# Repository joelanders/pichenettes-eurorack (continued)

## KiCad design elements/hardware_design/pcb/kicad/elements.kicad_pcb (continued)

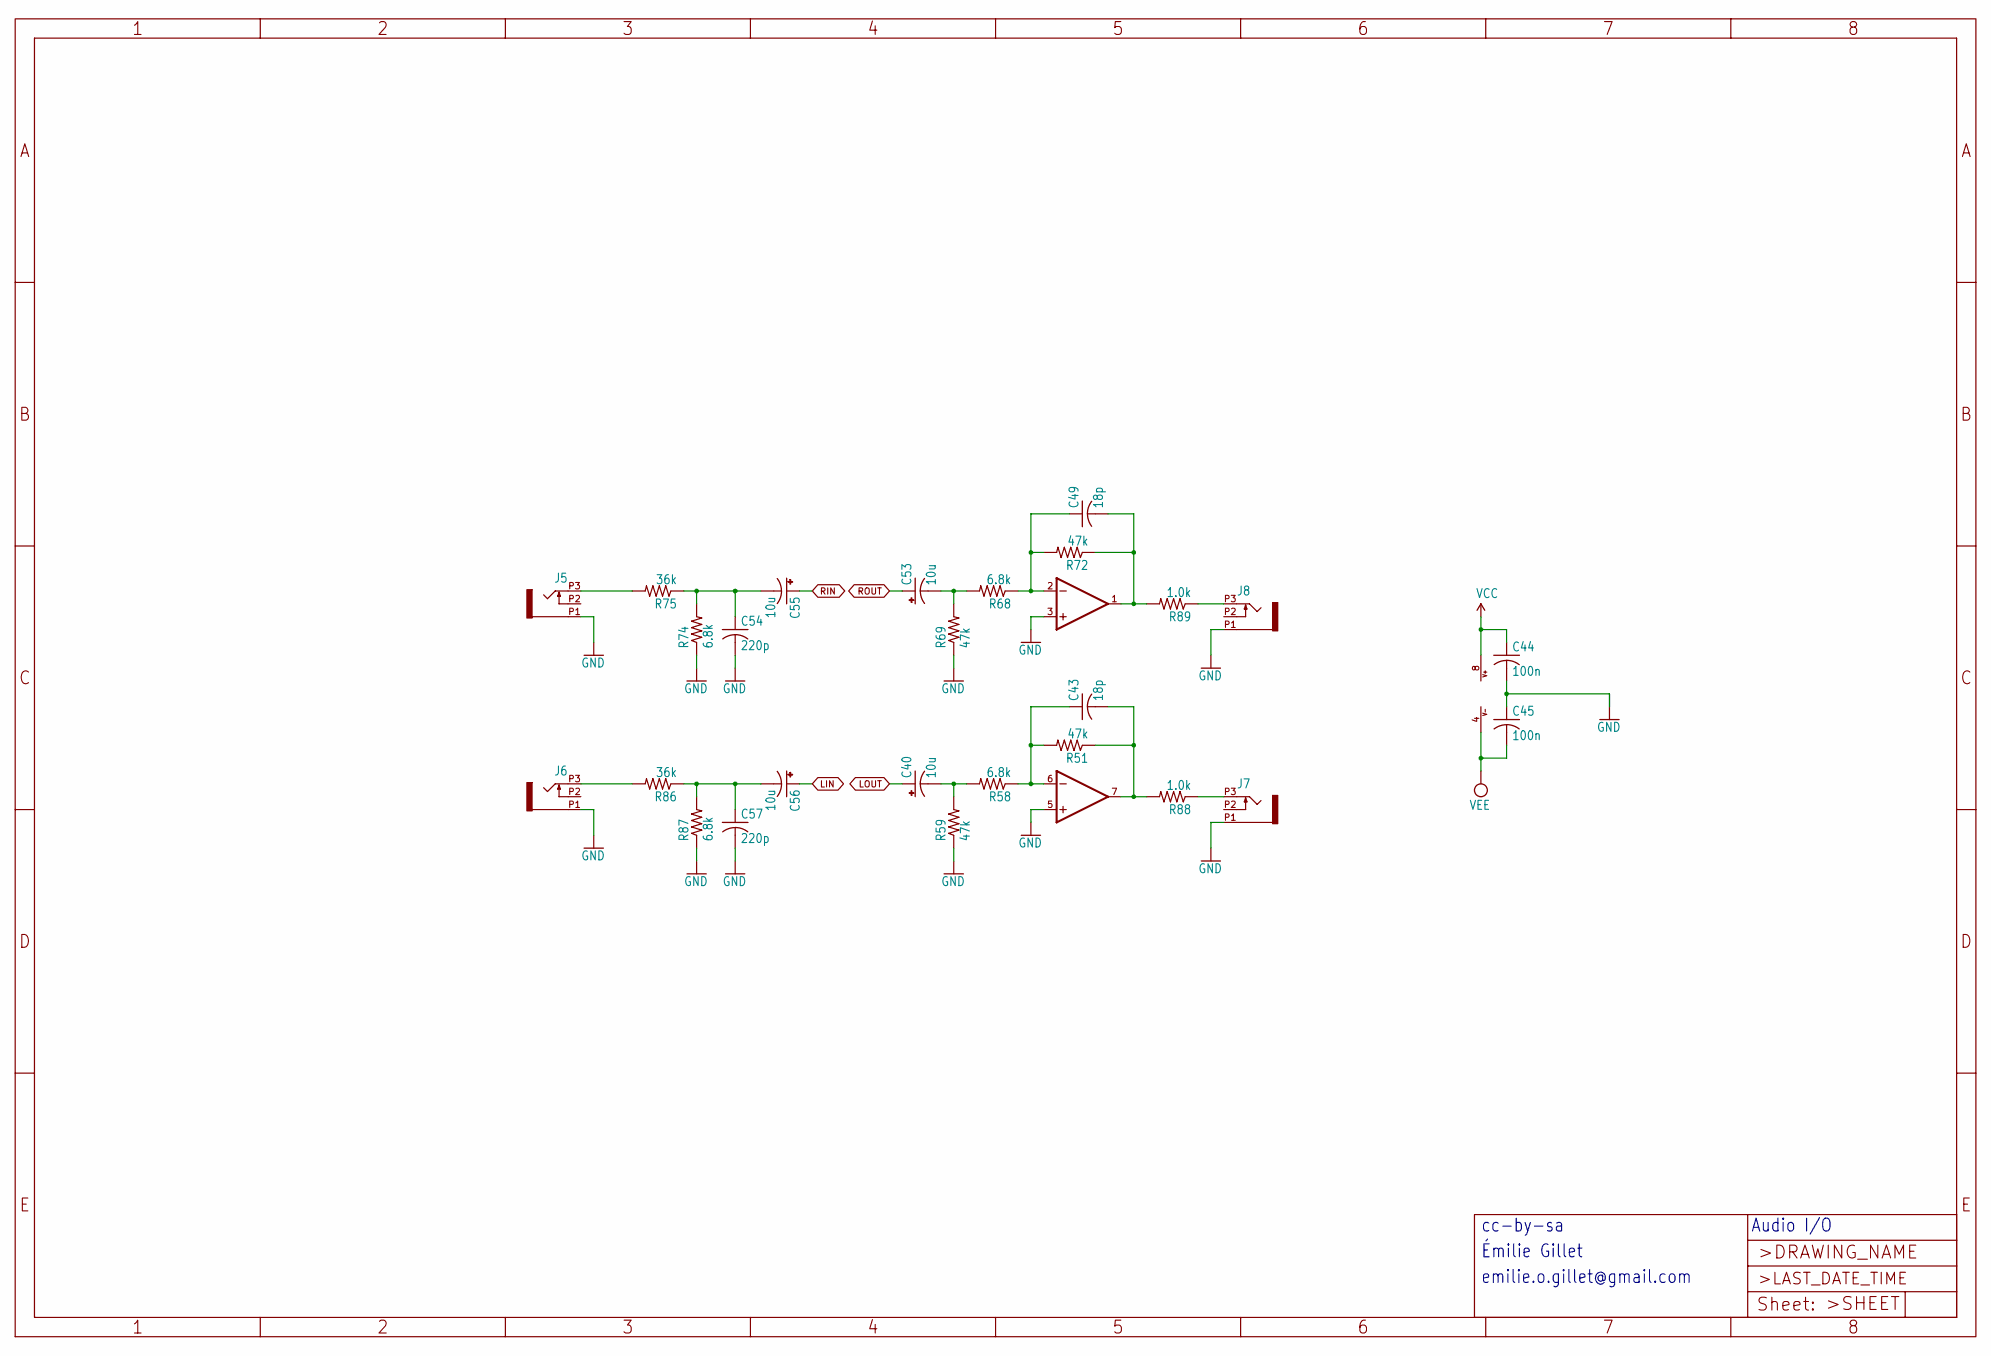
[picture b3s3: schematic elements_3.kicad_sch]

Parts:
C40, C53, C55, C56: 10u; PANASONIC_B
C43, C49: 18p; C0603
C44, C45: 100n; C0603
C54, C57: 220p; C0603
IC14: TL072; SO08
J5, J6, J7, J8: PJ301_THONKICONN6; WQP_PJ_301M6
R51, R59, R69, R72: 47k; R0603
R58, R68, R74, R87: 6.8k; R0603
R75, R86: 36k; R0603
R88, R89: 1.0k; R0603

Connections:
GND: C44.2, C45.1, C54.2, C57.2, IC14.3 (+IN), IC14.5 (+IN), J5.P1 (1), J6.P1 (1), J7.P1 (1), J8.P1 (1), R59.1, R69.1, R74.1, R87.1; also elsewhere on the board
LIN: C56.+; also elsewhere on the board
LOUT: C40.+; also elsewhere on the board
unnamed: C40.-, R58.2, R59.2
unnamed: C43.1, IC14.6 (-IN), R51.2, R58.1
unnamed: C43.2, IC14.7 (OUT), R51.1, R88.2
unnamed: C49.1, IC14.2 (-IN), R68.1, R72.2
unnamed: C49.2, IC14.1 (OUT), R72.1, R89.2
unnamed: C53.-, R68.2, R69.2
unnamed: C54.1, C55.-, R74.2, R75.1
unnamed: C56.-, C57.1, R86.1, R87.2
unnamed: J5.P3 (3), R75.2
unnamed: J6.P3 (3), R86.2
unnamed: J7.P3 (3), R88.1
unnamed: J8.P3 (3), R89.1
RIN: C55.+; also elsewhere on the board
ROUT: C53.+; also elsewhere on the board
VCC: C44.1, IC14.8 (V+); also elsewhere on the board
VEE: C45.2, IC14.4 (V-); also elsewhere on the board

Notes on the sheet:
emilie.o.gillet@gmail.com
Audio I/O
Émilie Gillet
cc-by-sa

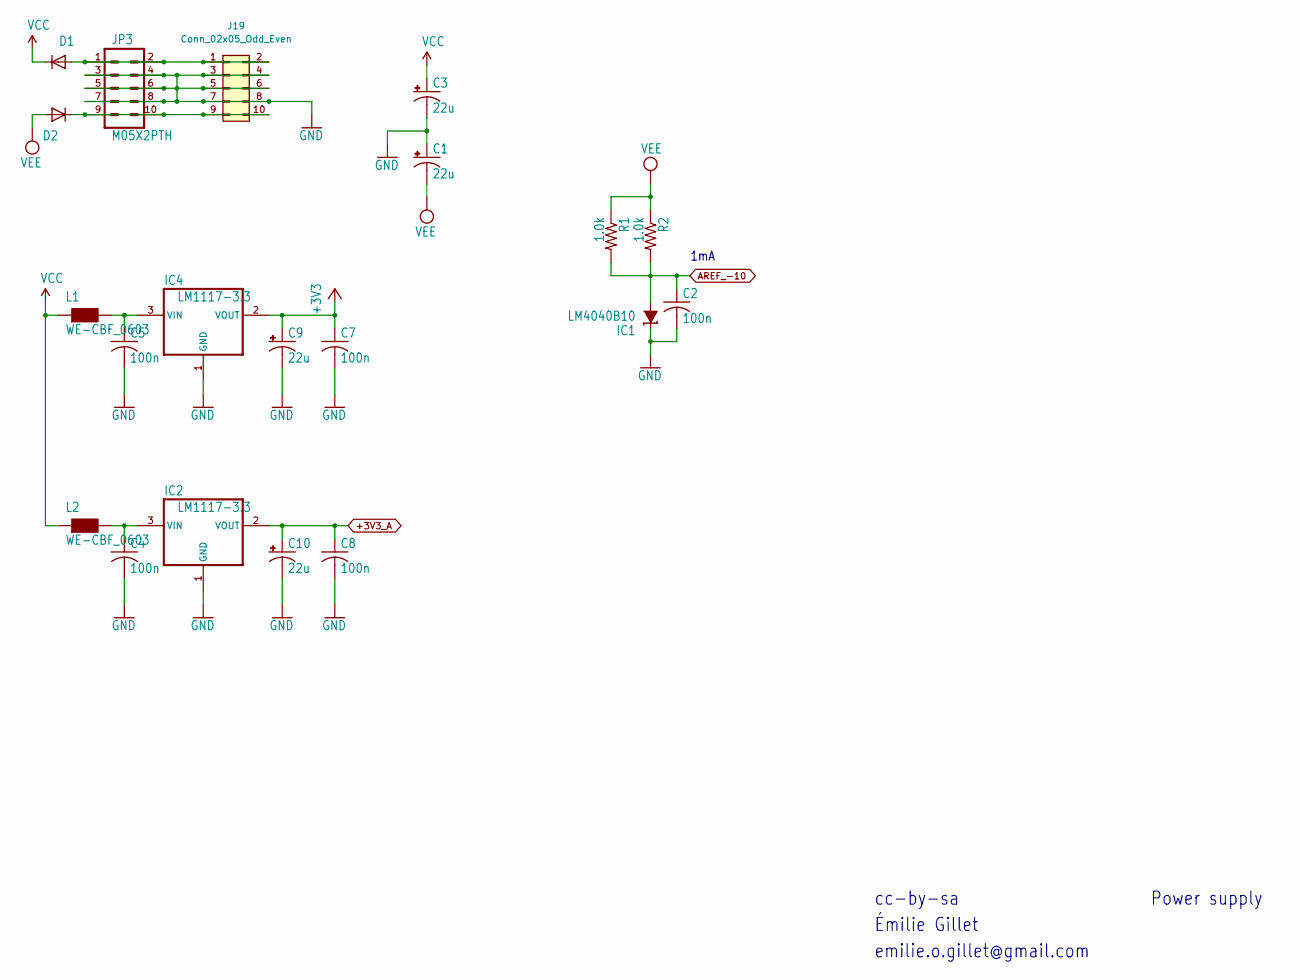
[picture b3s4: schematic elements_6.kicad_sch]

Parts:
C1, C3, C9, C10: 22u; PANASONIC_C
C2, C4, C5, C7, C8: 100n; C0603
D1, D2: 1N5819HW; SOD123
IC1: LM4040B10; DBZ_R-PDSO-G3
IC2, IC4: LM1117-3.3; SOT223
J19: Conn_02x05_Odd_Even; PinHeader_2x05_P2.54mm_Vertical_SMD
JP3: M05X2PTH; AVR_ICSP
L1, L2: WE-CBF_0603; 0603
R1, R2: 1.0k; R0603

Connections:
+3V3: C7.1, C9.+, IC4.2 (VOUT); also elsewhere on the board
+3V3_A: C8.1, C10.+, IC2.2 (VOUT); also elsewhere on the board
AREF_-10: C2.1, IC1.2 (A), R1.2, R2.2; also elsewhere on the board
GND: C1.+, C2.2, C3.-, C4.2, C5.2, C7.2, C8.2, C9.-, C10.-, IC1.1 (C), IC2.1 (GND), IC4.1 (GND), J19.3, J19.4, J19.5, J19.6, J19.7, J19.8, JP3.3, JP3.4, JP3.5, JP3.6, JP3.7, JP3.8; also elsewhere on the board
unnamed: C4.1, IC2.3 (VIN), L2.2
unnamed: C5.1, IC4.3 (VIN), L1.2
unnamed: D1.A, J19.1, J19.2, JP3.1, JP3.2
unnamed: D2.C, J19.9, J19.10, JP3.9, JP3.10
VCC: C3.+, D1.C, L1.1, L2.1; also elsewhere on the board
VEE: C1.-, D2.A, R1.1, R2.1; also elsewhere on the board

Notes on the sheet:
Émilie Gillet
emilie.o.gillet@gmail.com
Power supply
1mA
cc-by-sa

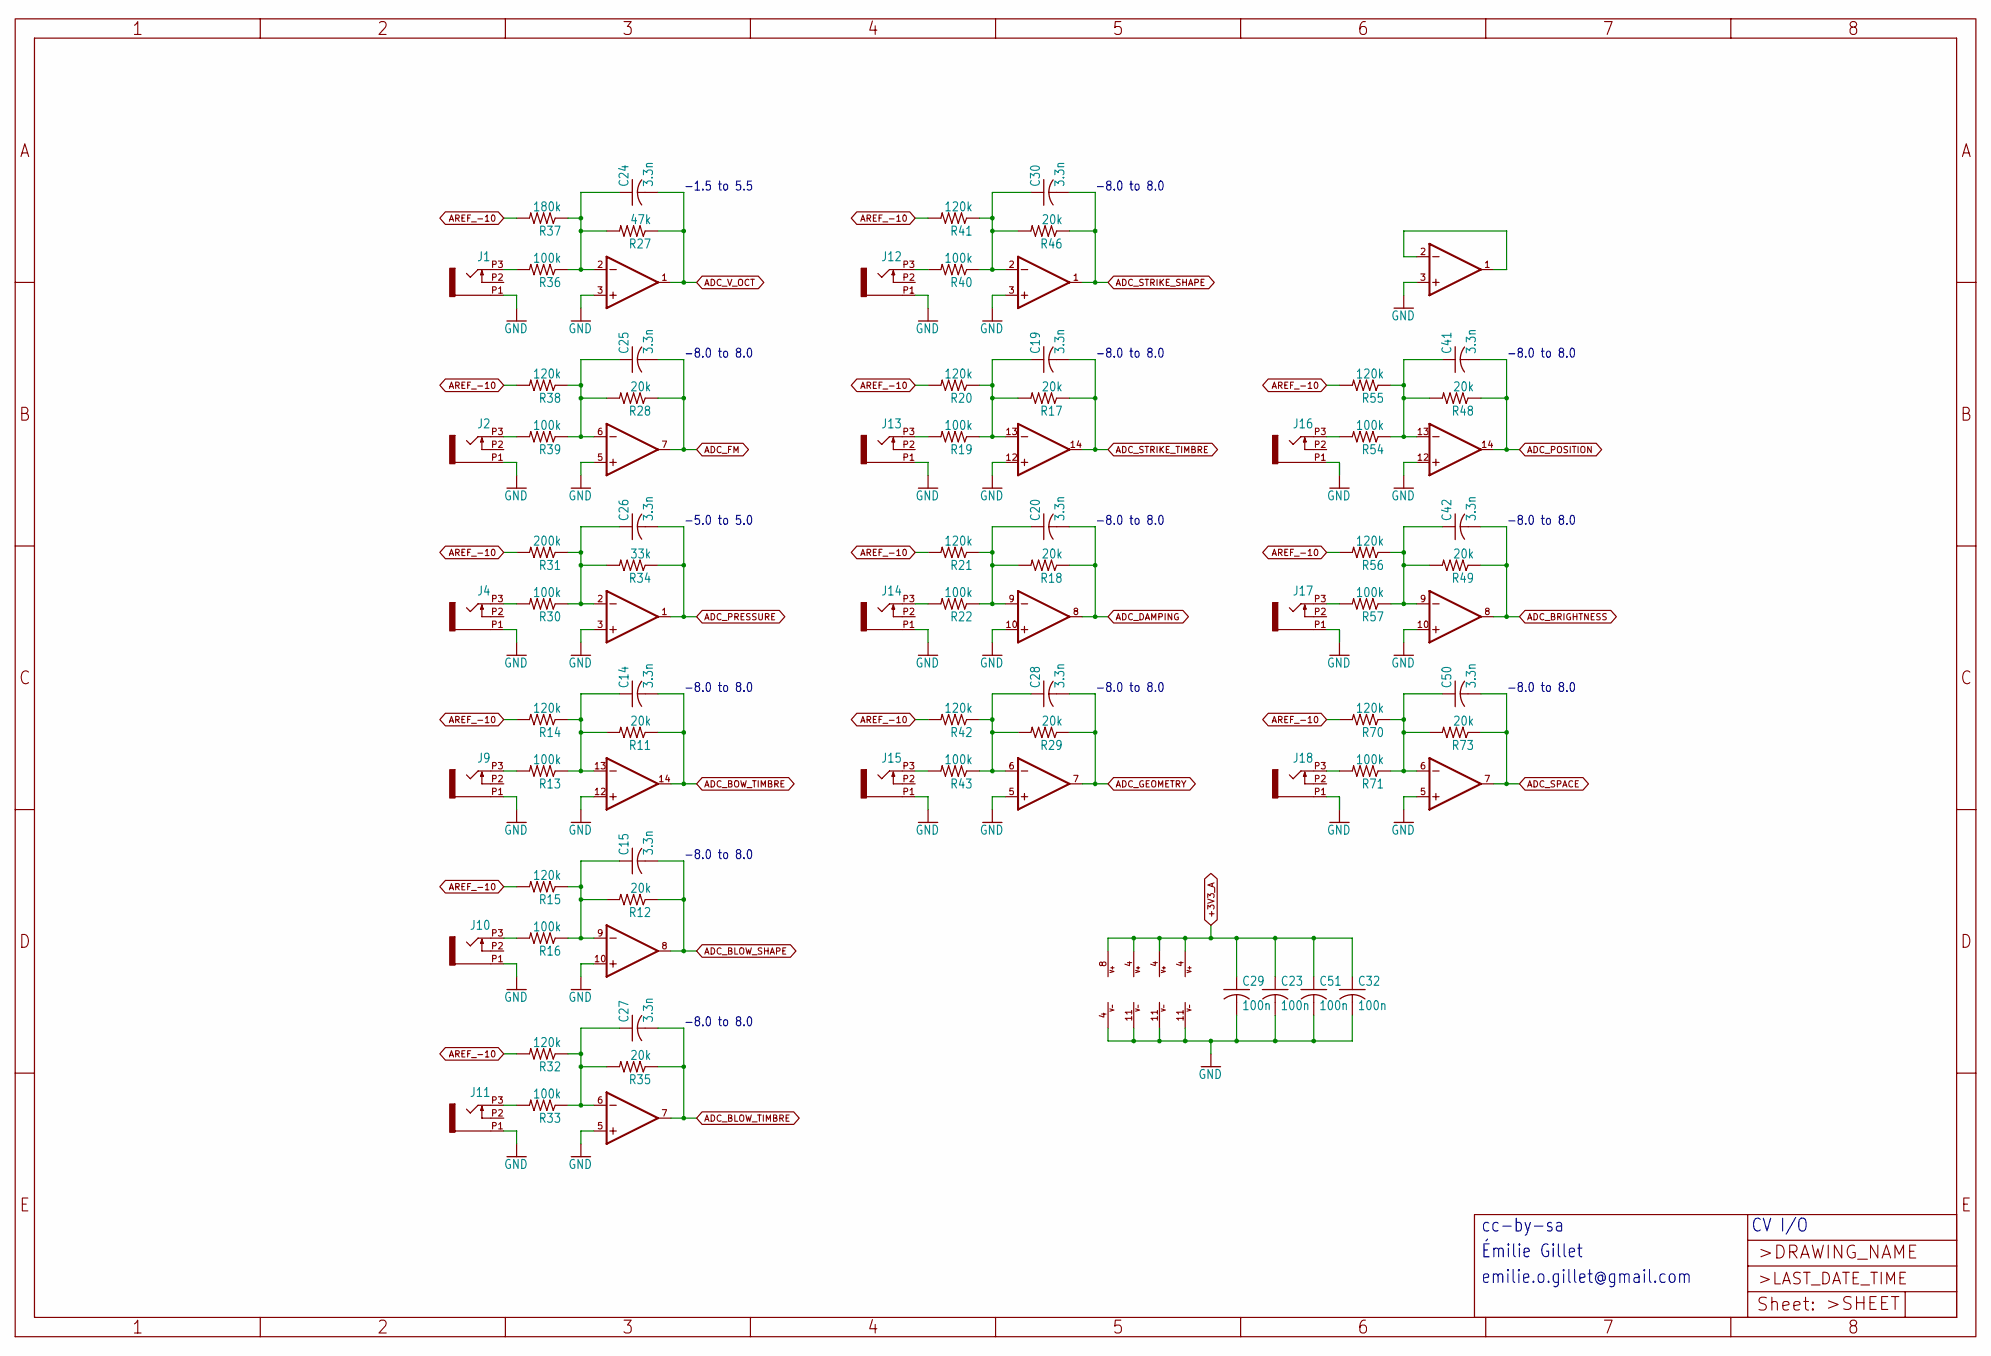
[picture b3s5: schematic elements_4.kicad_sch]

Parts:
C14, C15, C19, C20, C24, C25, C26, C27, C28, C30, C41, C42, C50: 3.3n; C0603
C23, C29, C32, C51: 100n; C0603
IC6, IC7, IC13: MCP6004; SO14
IC9: MCP6002; SO08
J1, J2, J4, J9, J10, J11, J12, J13, J14, J15, J16, J17, J18: PJ301_THONKICONN6; WQP_PJ_301M6
R11, R12, R17, R18, R28, R29, R35, R46, R48, R49, R73: 20k; R0603
R13, R16, R19, R22, R30, R33, R36, R39, R40, R43, R54, R57, R71: 100k; R0603
R14, R15, R20, R21, R32, R38, R41, R42, R55, R56, R70: 120k; R0603
R27: 47k; R0603
R31: 200k; R0603
R34: 33k; R0603
R37: 180k; R0603

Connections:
+3V3_A: C23.1, C29.1, C32.1, C51.1, IC6.4 (V+), IC7.4 (V+), IC9.8 (V+), IC13.4 (V+); also elsewhere on the board
ADC_BLOW_SHAPE: C15.2, IC6.8 (OUT), R12.1; also elsewhere on the board
ADC_BLOW_TIMBRE: C27.2, IC6.7 (OUT), R35.1; also elsewhere on the board
ADC_BOW_TIMBRE: C14.2, IC6.14 (OUT), R11.1; also elsewhere on the board
ADC_BRIGHTNESS: C42.2, IC13.8 (OUT), R49.1; also elsewhere on the board
ADC_DAMPING: C20.2, IC7.8 (OUT), R18.1; also elsewhere on the board
ADC_FM: C25.2, IC9.7 (OUT), R28.1; also elsewhere on the board
ADC_GEOMETRY: C28.2, IC7.7 (OUT), R29.1; also elsewhere on the board
ADC_POSITION: C41.2, IC13.14 (OUT), R48.1; also elsewhere on the board
ADC_PRESSURE: C26.2, IC6.1 (OUT), R34.1; also elsewhere on the board
ADC_SPACE: C50.2, IC13.7 (OUT), R73.1; also elsewhere on the board
ADC_STRIKE_SHAPE: C30.2, IC7.1 (OUT), R46.1; also elsewhere on the board
ADC_STRIKE_TIMBRE: C19.2, IC7.14 (OUT), R17.1; also elsewhere on the board
ADC_V_OCT: C24.2, IC9.1 (OUT), R27.1; also elsewhere on the board
AREF_-10: R14.2, R15.2, R20.2, R21.2, R31.2, R32.2, R37.2, R38.2, R41.2, R42.2, R55.2, R56.2, R70.2; also elsewhere on the board
GND: C23.2, C29.2, C32.2, C51.2, IC6.3 (+IN), IC6.5 (+IN), IC6.10 (+IN), IC6.11 (V-), IC6.12 (+IN), IC7.3 (+IN), IC7.5 (+IN), IC7.10 (+IN), IC7.11 (V-), IC7.12 (+IN), IC9.3 (+IN), IC9.4 (V-), IC9.5 (+IN), IC13.3 (+IN), IC13.5 (+IN), IC13.10 (+IN), IC13.11 (V-), IC13.12 (+IN), J1.P1 (1), J2.P1 (1), J4.P1 (1), J9.P1 (1), J10.P1 (1), J11.P1 (1), J12.P1 (1), J13.P1 (1), J14.P1 (1), J15.P1 (1), J16.P1 (1), J17.P1 (1), J18.P1 (1); also elsewhere on the board
unnamed: C14.1, IC6.13 (-IN), R11.2, R13.1, R14.1
unnamed: C15.1, IC6.9 (-IN), R12.2, R15.1, R16.1
unnamed: C19.1, IC7.13 (-IN), R17.2, R19.1, R20.1
unnamed: C20.1, IC7.9 (-IN), R18.2, R21.1, R22.1
unnamed: C24.1, IC9.2 (-IN), R27.2, R36.1, R37.1
unnamed: C25.1, IC9.6 (-IN), R28.2, R38.1, R39.1
unnamed: C26.1, IC6.2 (-IN), R30.1, R31.1, R34.2
unnamed: C27.1, IC6.6 (-IN), R32.1, R33.1, R35.2
unnamed: C28.1, IC7.6 (-IN), R29.2, R42.1, R43.1
unnamed: C30.1, IC7.2 (-IN), R40.1, R41.1, R46.2
unnamed: C41.1, IC13.13 (-IN), R48.2, R54.1, R55.1
unnamed: C42.1, IC13.9 (-IN), R49.2, R56.1, R57.1
unnamed: C50.1, IC13.6 (-IN), R70.1, R71.1, R73.2
unnamed: IC13.1 (OUT), IC13.2 (-IN)
unnamed: J1.P3 (3), R36.2
unnamed: J2.P3 (3), R39.2
unnamed: J4.P3 (3), R30.2
unnamed: J9.P3 (3), R13.2
unnamed: J10.P3 (3), R16.2
unnamed: J11.P3 (3), R33.2
unnamed: J12.P3 (3), R40.2
unnamed: J13.P3 (3), R19.2
unnamed: J14.P3 (3), R22.2
unnamed: J15.P3 (3), R43.2
unnamed: J16.P3 (3), R54.2
unnamed: J17.P3 (3), R57.2
unnamed: J18.P3 (3), R71.2

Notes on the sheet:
-8.0 to 8.0
-5.0 to 5.0
Émilie Gillet
CV I/O
-1.5 to 5.5
emilie.o.gillet@gmail.com
cc-by-sa

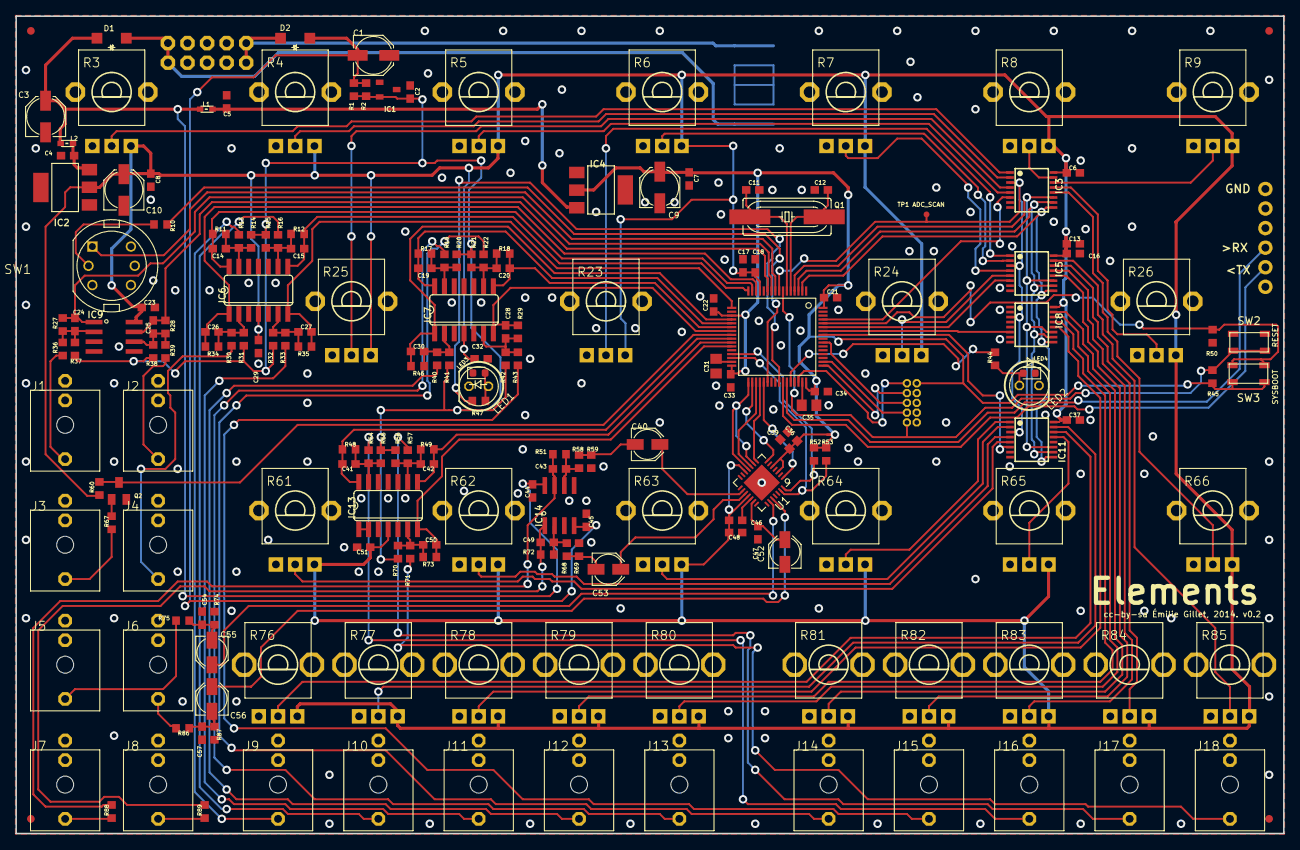
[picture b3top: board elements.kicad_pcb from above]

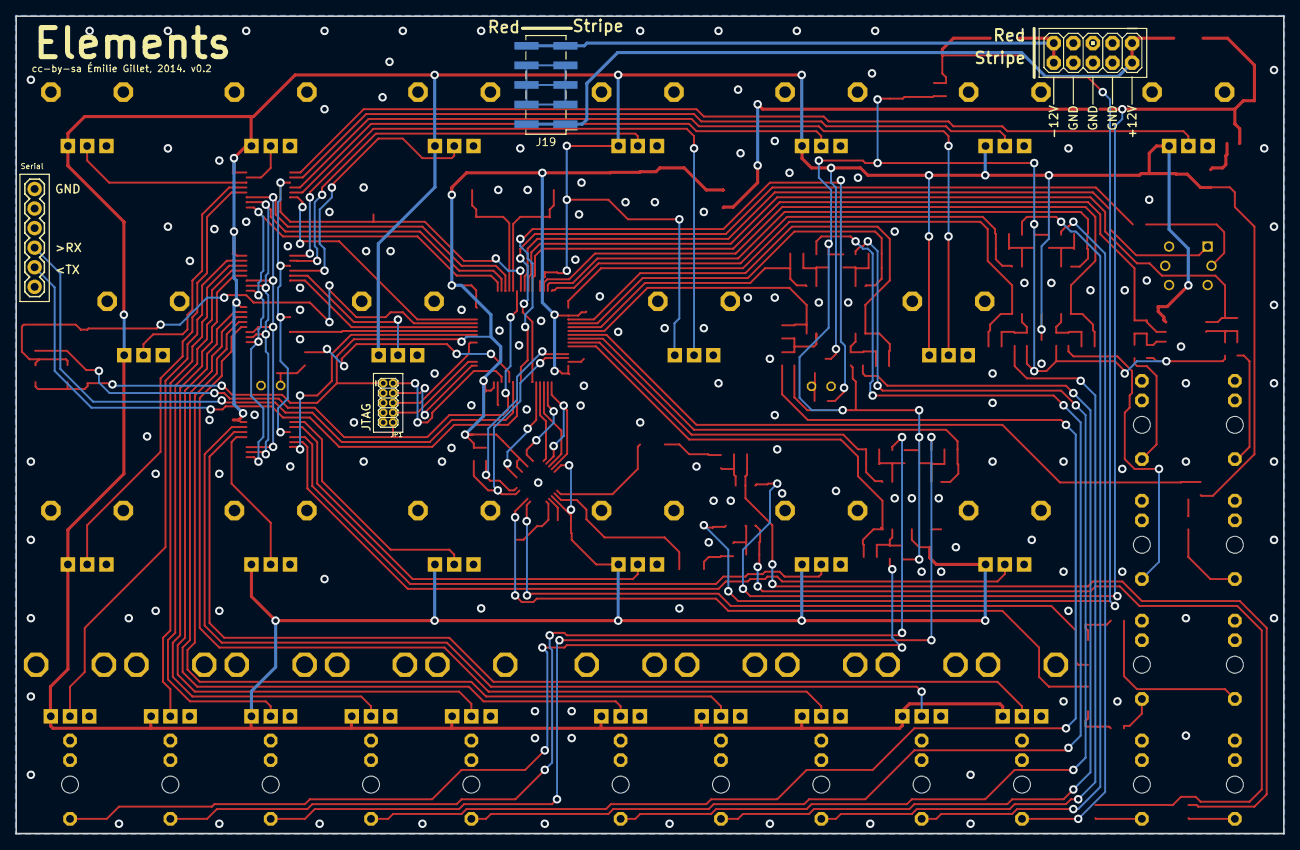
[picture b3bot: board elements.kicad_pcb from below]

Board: 2 copper layers, 164.5 x 106.0 mm, 199 parts (4 on the bottom side), 131 nets.

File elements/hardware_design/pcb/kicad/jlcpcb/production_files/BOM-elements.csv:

Comment,Designator,Footprint,LCSC
100n,C33,C0603,
MCP6004,IC7,SO14,
TL072,IC14,SO08,
100n,C4,C0603,
100n,C34,C0603,
PJ301_THONKICONN6,J16,WQP_PJ_301M6,
3.3n,C41,C0603,
PJ301_THONKICONN6,J2,WQP_PJ_301M6,
3.3n,C20,C0603,
ADC_TEST,TP1,PAD.03X.03,
3.3n,C50,C0603,
PJ301_THONKICONN6,J3,WQP_PJ_301M6,
18p,C43,C0603,
PJ301_THONKICONN6,J5,WQP_PJ_301M6,
120k,R56,R0603,
33,R10,R0603,
20k,R11,R0603,
220p,C54,C0603,
PJ301_THONKICONN6,J13,WQP_PJ_301M6,
20k,R28,R0603,
FIDUCIAL1X2,F2,FIDUCIAL-1X2,
1N5819HW,D2,SOD123,
20k,R46,R0603,
SSL-LX5093TC,LED1,LED5MM,
10kB,R63,ALPS_POT_VERTICAL_PS,
3.3n,C25,C0603,
10kB,R76,ALPS_POT_VERTICAL,
SSL-LX5093PC,LED2,LED5MM,
10u,C56,PANASONIC_B,
10kB,R66,ALPS_POT_VERTICAL_PS,
1.0k,R2,R0603,
47k,R51,R0603,
2.2k,R44,R0603,
10kB,R78,ALPS_POT_VERTICAL,
3.3n,C24,C0603,
47k,R69,R0603,
WE-CBF_0603,L1,0603,
18p,C12,C0603,
10k,R60,R0603,
6.8k,R87,R0603,
10kB,R77,ALPS_POT_VERTICAL,
22u,C9,PANASONIC_C,
100n,C32,C0603,
10kB,R64,ALPS_POT_VERTICAL_PS,
100n,C7,C0603,
100n,C13,C0603,
1.0k,R88,R0603,
100k,R16,R0603,
10kB,R5,ALPS_POT_VERTICAL_PS,
2.2k,R53,R0603,
100k,R40,R0603,
PJ301_THONKICONN6,J12,WQP_PJ_301M6,
EVQQ2,SW2,k2-1808 pushbutton switch,
47k,R27,R0603,
20k,R73,R0603,
PJ301_THONKICONN6,J18,WQP_PJ_301M6,
120k,R70,R0603,
PJ301_THONKICONN6,J8,WQP_PJ_301M6,
FIDUCIAL1X2,F4,FIDUCIAL-1X2,
100k,R54,R0603,
2.2k,R52,R0603,
3.3n,C27,C0603,
3.3n,C15,C0603,
10k,R50,R0603,
100n,C45,C0603,
6.8k,R68,R0603,
LM1117-3.3,IC2,SOT223,
FIDUCIAL1X2,F1,FIDUCIAL-1X2,
10kB,R65,ALPS_POT_VERTICAL_PS,
10u,C52,PANASONIC_B,
20k,R49,R0603,
1u,C17,C0603,
100k,R57,R0603,
EVQQ2,SW3,k2-1808 pushbutton switch,
100n,C21,C0603,
PJ301_THONKICONN6,J1,WQP_PJ_301M6,
100n,C29,C0603,
3.3n,C42,C0603,
100k,R30,R0603,
120k,R38,R0603,
PJ301_THONKICONN6,J15,WQP_PJ_301M6,
100n,C5,C0603,
10kB,R81,ALPS_POT_VERTICAL,
10kB,R61,ALPS_POT_VERTICAL_PS,
100n,C39,C0603,
MMBT3904,Q2,SOT23-BEC,
PJ301_THONKICONN6,J9,WQP_PJ_301M6,
10kB,R25,ALPS_POT_VERTICAL_PS,
4051PW,IC3,TSSOP16,
4051PW,IC5,TSSOP16,
20k,R17,R0603,
PJ301_THONKICONN6,J10,WQP_PJ_301M6,
120k,R41,R0603,
MCP6004,IC6,SO14,
100k,R13,R0603,
PJ301_THONKICONN6,J4,WQP_PJ_301M6,
10kB,R6,ALPS_POT_VERTICAL_PS,
3.3n,C30,C0603,
10kB,R79,ALPS_POT_VERTICAL,
100n,C8,C0603,
220p,C57,C0603,
10kB,R3,ALPS_POT_VERTICAL_PS,
3.3n,C28,C0603,
100k,R43,R0603,
100k,R67,R0603,
20k,R29,R0603,
2.2u,C35,C0805,
22u,C1,PANASONIC_C,
120k,R32,R0603,
10u,C55,PANASONIC_B,
10kB,R9,ALPS_POT_VERTICAL_PS,
STM32F405RGT6,IC10,TQFP-10X10-64,
PJ301_THONKICONN6,J11,WQP_PJ_301M6,
SSL-LX5093TC,LED3,LED_0603_1608Metric,
100n,C51,C0603,
PJ301_THONKICONN6,J6,WQP_PJ_301M6,
120k,R42,R0603,
47k,R72,R0603,
18p,C11,C0603,
36k,R86,R0603,
WM8731CLSEFL,U1,QFN-28-1EP_5x5mm_P0.5mm_EP3.35x3.35mm,
100n,C37,C0603,
20k,R12,R0603,
120k,R20,R0603,
100k,R33,R0603,
10kB,R7,ALPS_POT_VERTICAL_PS,
PJ301_THONKICONN6,J14,WQP_PJ_301M6,
100k,R22,R0603,
1u,C36,C0603,
100k,R71,R0603,
120k,R21,R0603,
10kB,R8,ALPS_POT_VERTICAL_PS,
180k,R37,R0603,
100n,C44,C0603,
10kB,R80,ALPS_POT_VERTICAL,
120k,R55,R0603,
SW_MEC_5G_2LED,SW1,C&K_D6R,
10kB,R82,ALPS_POT_VERTICAL,
3.3n,C26,C0603,
6.8k,R58,R0603,
18p,C49,C0603,
10kB,R83,ALPS_POT_VERTICAL,
100k,R36,R0603,
200k,R31,R0603,
120k,R15,R0603,
100n,C2,C0603,
6.8k,R74,R0603,
10kB,R84,ALPS_POT_VERTICAL,
20k,R18,R0603,
PJ301_THONKICONN6,J17,WQP_PJ_301M6,
100n,C47,C0603,
10u,C53,PANASONIC_B,
20k,R35,R0603,
4051PW,IC11,TSSOP16,
47k,R59,R0603,
FIDUCIAL1X2,F3,FIDUCIAL-1X2,
22u,C3,PANASONIC_C,
SSL-LX5093PC,LED4,LED_0603_1608Metric,
100n,C16,C0603,
100n,C23,C0603,
MCP6004,IC13,SO14,
100k,R19,R0603,
1u,C48,C0603,
10k,R45,R0603,
1.0k,R89,R0603,
3.3n,C14,C0603,
2.2u,C31,C0805,
10kB,R85,ALPS_POT_VERTICAL,
MCP6002,IC9,SO08,
36k,R75,R0603,
10kB,R26,ALPS_POT_VERTICAL_PS,
LM1117-3.3,IC4,SOT223,
10kB,R24,ALPS_POT_VERTICAL_PS,
20k,R48,R0603,
33k,R34,R0603,
3.3n,C19,C0603,
PJ301_THONKICONN6,J7,WQP_PJ_301M6,
100n,C22,C0603,
10kB,R23,ALPS_POT_VERTICAL_PS,
100k,R39,R0603,
4051PW,IC8,TSSOP16,
1.0k,R1,R0603,
8MHz,Q1,HC49UP,
100n,C46,C0603,
2.2k,R47,R0603,
1N5819HW,D1,SOD123,
10kB,R62,ALPS_POT_VERTICAL_PS,
120k,R14,R0603,
22u,C10,PANASONIC_C,
10u,C40,PANASONIC_B,
10kB,R4,ALPS_POT_VERTICAL_PS,
100n,C6,C0603,
WE-CBF_0603,L2,0603,
100n,C18,C0603,
LM4040B10,IC1,DBZ_R-PDSO-G3,
M06SIP,JP2,1X06,
M05X2PTH,JP3,AVR_ICSP,
M05X2MINIJTAG,JP1,2X5-1.27,
Conn_02x05_Odd_Even,J19,PinHeader_2x05_P2.54mm_Vertical_SMD,

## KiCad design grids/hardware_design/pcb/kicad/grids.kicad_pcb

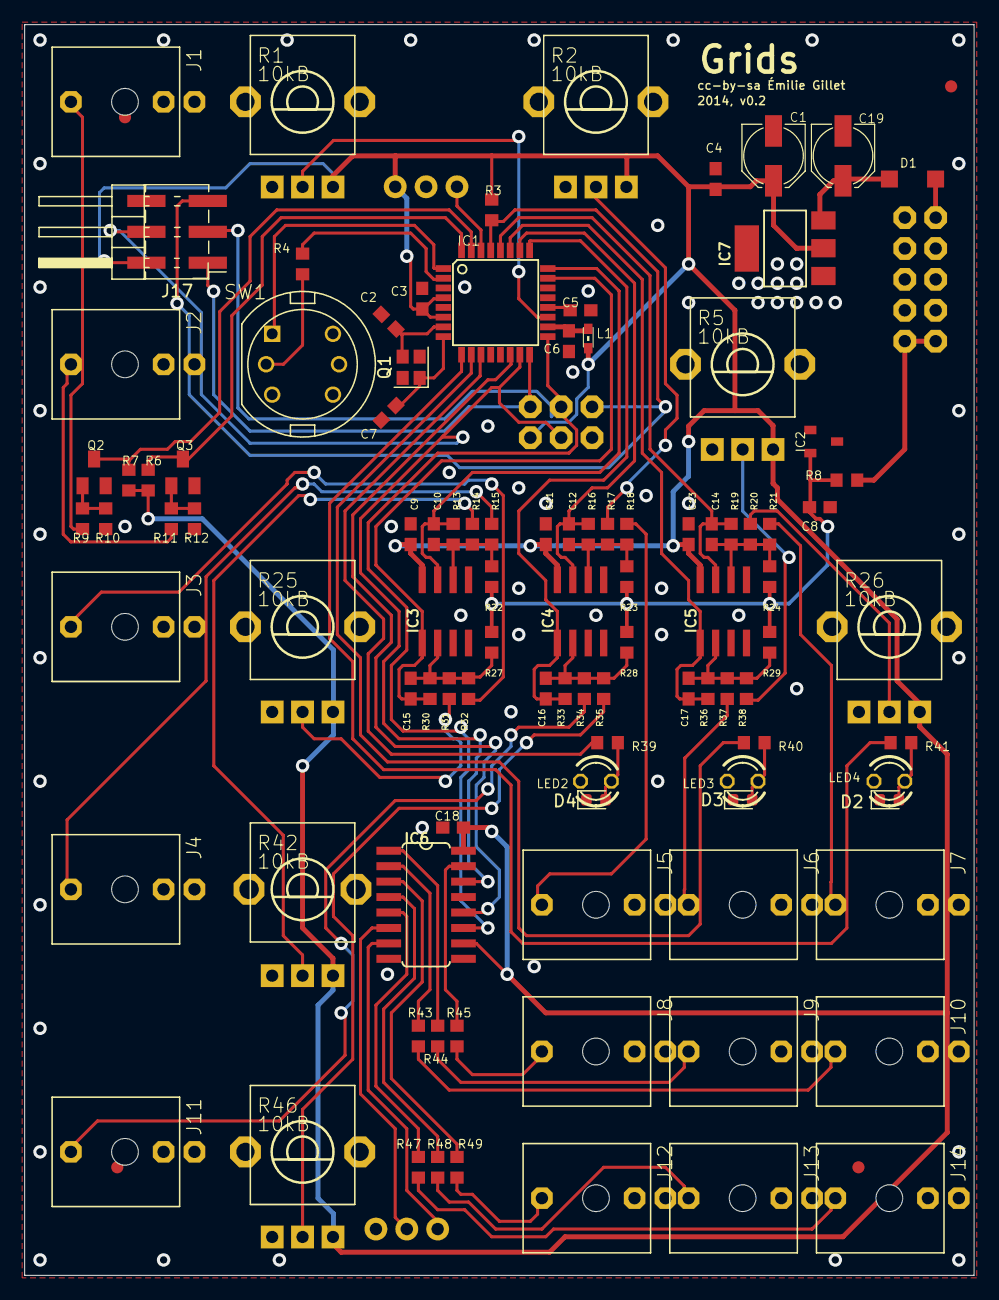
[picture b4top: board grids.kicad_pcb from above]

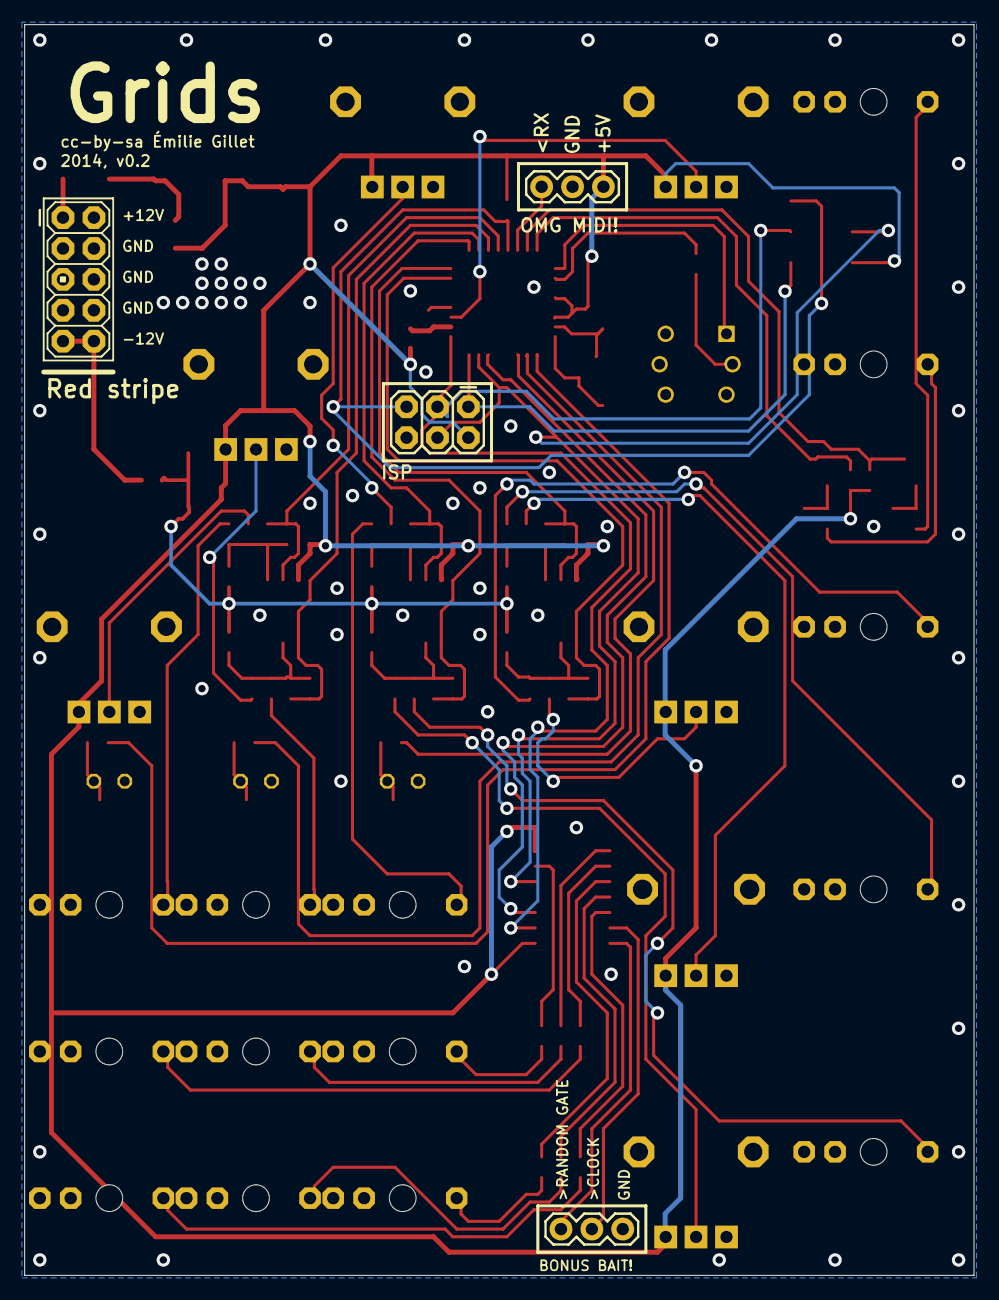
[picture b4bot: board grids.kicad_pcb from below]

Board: 2 copper layers, 78.1 x 102.9 mm, 110 parts (4 on the bottom side), 70 nets.

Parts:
C1, C19: 22u; PANASONIC_C
C2, C7: 18p; C0603
C3, C4, C5, C6, C9, C11, C13, C18: 100n; C0603
C8: 470n; C0603
C10, C12, C14, C15, C16, C17: 10n; C0603
D1: 1N5819HW; SOD123
D2, D3, D4: LED; LED_0603_1608Metric
F1, F2, F3, F4: FIDUCIAL1X2; FIDUCIAL-1X2
IC1: ATMEGA328P-AU; TQFP32-08
IC2: LM4040 5.0V; DBZ_R-PDSO-G3
IC3, IC4, IC5: MCP6002; SO08
IC6: 74595D; SO16
IC7: LM1117-5.0; SOT223
J1, J2, J3, J4, J5, J6, J7, J8, J9, J10, J11, J12, J13, J14: PJ301WQP; WQP_PJ_301M6
J15: AVR_SPI_PRG_6PTH; 2X3
J16: M05X2PTH; AVR_ICSP
J17: AVR_SPI_PRG_6PTH; PinHeader_2x03_P2.54mm_Horizontal_SMD
JP1, JP2: M03PTH; 1X03
L1: WE-CBF_0603; 0603
LED2, LED3, LED4: LED3MM
Q1: 20MHz; Crystal_SMD_2520-4Pin_2.5x2.0mm
Q2, Q3: MMBT3904; SOT23-BEC
R1, R2, R5, R25, R26, R46: 10kB; ALPS_POT_VERTICAL_PS
R3, R6, R7, R8: 10k; R0603
R4, R39, R40, R41: 100; R0603
R9, R11, R13, R14, R15, R16, R17, R18, R19, R20, R21, R22, R23, R24, R27, R28, R29, R30, R31, R32, R33, R34, R35, R36, R37, R38: 100k; R0603
R10, R12: 1M; R0603
R42: 10kB; ALPS_POT_VERTICAL_PS4
R43, R44, R45, R47, R48, R49: 1.0k; R0603
SW1: SW_MEC_5G_2LED; C&K_D6R

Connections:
+5V: C1.+, C3.1, C4.1, C9.1, C11.1, C13.1, C18.1, IC1.4 (VCC@1), IC1.6 (VCC@2), IC3.8 (V+), IC4.8 (V+), IC5.8 (V+), IC6.10 (SCL), IC6.16 (VCC), IC7.2 (VOUT), J15.2, J17.2, JP2.3, L1.1, R1.P$1 (E), R2.P$1 (E), R3.2, R5.P$1 (E), R6.2, R7.2, R25.P$1 (E), R26.P$1 (E), R42.P$1 (E), R46.P$1 (E)
/AREF: C5.1, IC1.20 (AREF)
/CH1_CV: C12.2, IC1.26 (PC3(ADC3)), IC4.7 (OUT), R16.2
/CH2_CV: C17.2, IC1.27 (PC4(ADC4/SDA)), IC5.1 (OUT), R36.2
/CH3_CV: C14.2, IC1.28 (PC5(ADC5/SCL)), IC5.7 (OUT), R19.2
/IN_CLOCK: IC1.31 (PD1(TXD)), Q2.C, R7.1
/IN_MIDI: IC1.30 (PD0(RXD)), JP2.1
/IN_RESET: IC1.32 (PD2(INT0)), Q3.C, R6.1
/LED_CH1: IC1.11 (PD7(AIN1)), R39.1
/LED_CH2: IC1.10 (PD6(AIN0)), R40.1
/LED_CH3: IC1.9 (PD5(T1)), R41.1
/LED_CLOCK: IC1.2 (PD4(XCK/T0)), R4.1
/MISO: IC1.16 (PB4(MISO)), J15.1, J17.1
/MOSI: IC1.15 (PB3(MOSI/OC2)), IC6.14 (SER), J15.4, J17.4
/REF_-5: C8.1, IC2.2 (A), R8.2, R22.1, R23.1, R24.1, R27.1, R28.1, R29.1
/RESET: IC1.29 (PC6(/RESET)), J15.5, J17.5, R3.1
/RND_CV: C16.2, IC1.25 (PC2(ADC2)), IC4.1 (OUT), R33.2
/SCK: IC1.17 (PB5(SCK)), IC6.11 (SCK), J15.3, J17.3
/SS: IC1.14 (PB2(SS/OC1B)), IC6.12 (RCK)
/SW_RESET: IC1.1 (PD3(INT1)), SW1.1
/TEMPO: IC1.19 (ADC6), R1.P$2 (S)
/X_CV: C15.2, IC1.23 (PC0(ADC0)), IC3.1 (OUT), R30.2
/Y_CV: C10.2, IC1.24 (PC1(ADC1)), IC3.7 (OUT), R13.2
GND: C1.-, C2.1, C3.2, C4.2, C5.2, C6.2, C7.1, C8.2, C9.2, C11.2, C13.2, C18.2, C19.-, D2.1 (K), D3.1 (K), D4.1 (K), IC1.3 (GND@1), IC1.5 (AGND), IC1.21 (GND@2), IC2.1 (C), IC3.3 (+IN), IC3.4 (V-), IC3.5 (+IN), IC4.3 (+IN), IC4.4 (V-), IC4.5 (+IN), IC5.3 (+IN), IC5.4 (V-), IC5.5 (+IN), IC6.8 (GND), IC6.13 (G), IC7.1 (GND), J1.GND (1), J2.GND (1), J3.GND (1), J4.GND (1), J5.GND (1), J6.GND (1), J7.GND (1), J8.GND (1), J9.GND (1), J10.GND (1), J11.GND (1), J12.GND (1), J13.GND (1), J14.GND (1), J15.6, J16.3, J16.4, J16.5, J16.6, J16.7, J16.8, J17.6, JP1.1, JP2.2, LED2.K (C), LED3.K (C), LED4.K (C), Q2.E, Q3.E, R1.P$3 (A), R2.P$3 (A), R5.P$3 (A), R10.1, R12.1, R25.P$3 (A), R26.P$3 (A), R42.P$3 (A), R46.P$3 (A), SW1.3 (K), SW1.4 (A)
unnamed: C2.2, IC1.7 (PB6(XTAL1/TOSC1)), Q1.3
unnamed: C6.1, IC1.18 (AVCC), L1.2
unnamed: C7.2, IC1.8 (PB7(XTAL2/TOSC2)), Q1.1
unnamed: C10.1, IC3.6 (-IN), R13.1, R14.2, R15.2, R22.2
unnamed: C12.1, IC4.6 (-IN), R16.1, R17.2, R18.2, R23.2
unnamed: C14.1, IC5.6 (-IN), R19.1, R20.2, R21.2, R24.2
unnamed: C15.1, IC3.2 (-IN), R27.2, R30.1, R31.2, R32.2
unnamed: C16.1, IC4.2 (-IN), R28.2, R33.1, R34.2, R35.2
unnamed: C17.1, IC5.2 (-IN), R29.2, R36.1, R37.2, R38.2
unnamed: D1.A, J16.1
unnamed: IC6.1 (QB), R44.1
unnamed: IC6.2 (QC), R43.1
unnamed: IC6.3 (QD), R49.1
unnamed: IC6.4 (QE), R48.1
unnamed: IC6.5 (QF), R47.1
unnamed: IC6.6 (QG), JP1.2
unnamed: IC6.7 (QH), JP1.3
unnamed: IC6.15 (QA), R45.1
unnamed: J1.TIP (2), R9.2
unnamed: J2.TIP (2), R11.2
unnamed: J3.TIP (2), R32.1
unnamed: J4.TIP (2), R15.1
unnamed: J5.TIP (2), R18.1
unnamed: J6.TIP (2), R37.1
unnamed: J7.TIP (2), R21.1
unnamed: J8.TIP (2), R45.2
unnamed: J9.TIP (2), R44.2
unnamed: J10.TIP (2), R43.2
unnamed: J11.TIP (2), R34.1
unnamed: J12.TIP (2), R49.2
unnamed: J13.TIP (2), R48.2
unnamed: J14.TIP (2), R47.2
unnamed: Q2.B, R9.1, R10.2
unnamed: Q3.B, R11.1, R12.2
unnamed: R14.1, R42.P$2 (S)
unnamed: R2.P$2 (S), R17.1
unnamed: R20.1, R26.P$2 (S)
unnamed: R25.P$2 (S), R31.1
unnamed: R35.1, R46.P$2 (S)
unnamed: R5.P$2 (S), R38.1
unnamed: D4.2 (A), LED2.A, R39.2
unnamed: D3.2 (A), LED3.A, R40.2
unnamed: D2.2 (A), LED4.A, R41.2
unnamed: R4.2, SW1.2
VCC: C19.+, D1.C, IC7.3 (VIN)
VEE: J16.9, J16.10, R8.1

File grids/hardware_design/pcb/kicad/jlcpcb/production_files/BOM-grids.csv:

Comment,Designator,Footprint,LCSC
74595D,IC6,SO16,
100k,R21,R0603,
100k,R22,R0603,
PJ301WQP,J4,WQP_PJ_301M6,
1.0k,R48,R0603,
PJ301WQP,J13,WQP_PJ_301M6,
470n,C8,C0603,
100n,C11,C0603,
PJ301WQP,J9,WQP_PJ_301M6,
PJ301WQP,J8,WQP_PJ_301M6,
10k,R8,R0603,
10n,C17,C0603,
100n,C18,C0603,
22u,C1,PANASONIC_C,
100n,C9,C0603,
100k,R18,R0603,
100k,R19,R0603,
PJ301WQP,J6,WQP_PJ_301M6,
LM4040 5.0V,IC2,DBZ_R-PDSO-G3,
100n,C13,C0603,
10n,C12,C0603,
100k,R33,R0603,
1N5819HW,D1,SOD123,
10kB,R1,ALPS_POT_VERTICAL_PS,
100k,R20,R0603,
1.0k,R49,R0603,
10kB,R42,ALPS_POT_VERTICAL_PS4,
MCP6002,IC5,SO08,
100k,R38,R0603,
10n,C10,C0603,
MCP6002,IC3,SO08,
1M,R10,R0603,
MMBT3904,Q3,SOT23-BEC,
22u,C19,PANASONIC_C,
MMBT3904,Q2,SOT23-BEC,
FIDUCIAL1X2,F3,FIDUCIAL-1X2,
AVR_SPI_PRG_6PTH,J17,PinHeader_2x03_P2.54mm_Horizontal_SMD,
PJ301WQP,J10,WQP_PJ_301M6,
100k,R24,R0603,
PJ301WQP,J3,WQP_PJ_301M6,
MCP6002,IC4,SO08,
10k,R6,R0603,
100k,R36,R0603,
10k,R3,R0603,
100k,R34,R0603,
ATMEGA328P-AU,IC1,TQFP32-08,
100,R41,R0603,
10kB,R2,ALPS_POT_VERTICAL_PS,
18p,C7,C0603,
100k,R32,R0603,
LED3MM,LED2,LED3MM,
100k,R15,R0603,
1.0k,R43,R0603,
1.0k,R45,R0603,
100n,C6,C0603,
PJ301WQP,J7,WQP_PJ_301M6,
100n,C3,C0603,
100k,R23,R0603,
100,R4,R0603,
100k,R17,R0603,
100k,R29,R0603,
LM1117-5.0,IC7,SOT223,
1M,R12,R0603,
100k,R37,R0603,
PJ301WQP,J11,WQP_PJ_301M6,
100k,R30,R0603,
10n,C15,C0603,
100k,R35,R0603,
FIDUCIAL1X2,F2,FIDUCIAL-1X2,
1.0k,R47,R0603,
PJ301WQP,J1,WQP_PJ_301M6,
100k,R16,R0603,
WE-CBF_0603,L1,0603,
100k,R28,R0603,
100n,C4,C0603,
PJ301WQP,J5,WQP_PJ_301M6,
20MHz,Q1,Crystal_SMD_2520-4Pin_2.5x2.0mm,
LED3MM,LED3,LED3MM,
10kB,R25,ALPS_POT_VERTICAL_PS,
100k,R31,R0603,
PJ301WQP,J14,WQP_PJ_301M6,
LED,D2,LED_0603_1608Metric,
LED,D4,LED_0603_1608Metric,
10n,C14,C0603,
FIDUCIAL1X2,F1,FIDUCIAL-1X2,
10kB,R46,ALPS_POT_VERTICAL_PS,
100k,R27,R0603,
100n,C5,C0603,
1.0k,R44,R0603,
PJ301WQP,J2,WQP_PJ_301M6,
10k,R7,R0603,
100k,R13,R0603,
LED,D3,LED_0603_1608Metric,
10kB,R5,ALPS_POT_VERTICAL_PS,
100,R40,R0603,
100k,R14,R0603,
FIDUCIAL1X2,F4,FIDUCIAL-1X2,
10n,C16,C0603,
LED3MM,LED4,LED3MM,
10kB,R26,ALPS_POT_VERTICAL_PS,
100k,R11,R0603,
PJ301WQP,J12,WQP_PJ_301M6,
100,R39,R0603,
18p,C2,C0603,
100k,R9,R0603,
SW_MEC_5G_2LED,SW1,C&K_D6R,
M03PTH,JP1,1X03,
AVR_SPI_PRG_6PTH,J15,2X3,
M05X2PTH,J16,AVR_ICSP,
M03PTH,JP2,1X03,
